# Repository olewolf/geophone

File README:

Geophone is an amplifier and a frequency analyzer for geometric sensors
such as the SM-24 geophone element from ION Geophysical Corp.

The amplifier is provided as an Arduino shield and the frequency analyzer is
implemented in software on the Arduino.  Because of the memory usage an
Arduino Mega or an Arduino Due is required.  Other Arduino versions with
at least 4 Kbytes of SRAM will require modifications in the code.

The Arduino code is richly commented and should be easy to understand and/or
modify.

For the Arduino Mega, use a single-supply operational amplifier capable of
working at 5V (such as an OP213) and set a jumper on JP3 to 5V mode.  For
the Arduino Due, use a single-supply operational amplifier working at 3.3V
(such as a TLC272 or an LT1215) to avoid damaging the Arduino's analog input.
JP3 should be placed in 3.3 mode.

Every second the Arduino software reports frequency components from 0 to 256
Hz and their measured amplitudes for amplitudes that exceed a programmed
threshold over the serial port.  The amplitudes are not calibrated; you will
have to perform a calibration yourself to translate the amplitudes into
ground movement in, e.g., meters per second.

The threshold may be changed by transmitting a new value followed by a
newline character.  The threshold is stored in EEPROM.

The frequency analysis lends itself directly to a 3D (or colored) time/
frequency plot that displays the intensities of different frequencies versus
time.  The Scilab script geoplot.sce reads a log file with the output and
generates such an image; geophone.log is a short sample of the output.

Geosampler.ino is a simple piece of software that samples the geophone
output at a rate of 512 samples per second and outputs the values over the
serial port.

read-serial-log.c provides sample C code that reads the serial output from
Geophone.ino and adds a timestamp.  The output may be plotted using the
createheatmap.pl perl script, which generates a JPEG file with the graphical
output.

Inquiries via the Github issue tracker, please.  This way, others may benefit
from the answers.

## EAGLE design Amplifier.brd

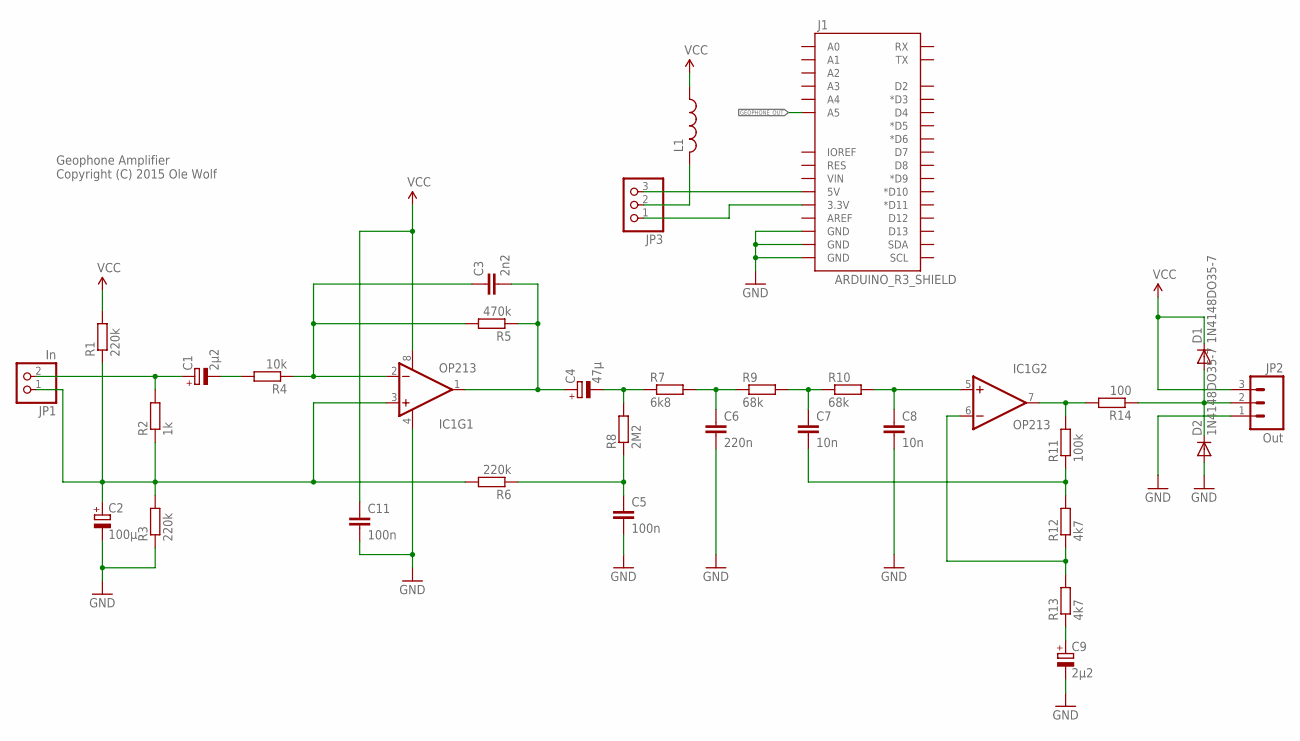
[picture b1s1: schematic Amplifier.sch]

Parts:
C1, C9: 2µ2; E2-5
C2: 100µ; E2-5
C3: 2n2; C025-025X050
C4: 47µ; E2-5
C5, C11: 100n; C025-025X050
C6: 220n; C025-025X050
C7, C8: 10n; C025-025X050
D1, D2: 1N4148DO35-7; DO35-7
IC1: OP213; DIP08
J1: ARDUINO_R3_SHIELD; UNO_R3_SHIELD
JP1: In; 1X02
JP2: Out; 1X03_LONGPADS
JP3: PINHD-1X3; 1X03
L1: L-US0207/2V; 0207/2V
R1, R3, R6: 220k; 0207/12
R2: 1k; 0207/12
R4: 10k; 0207/12
R5: 470k; 0207/12
R7: 6k8; 0207/12
R8: 2M2; 0207/12
R9, R10: 68k; 0207/12
R11: 100k; 0207/12
R12, R13: 4k7; 0207/12
R14: 100; 0207/12

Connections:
GEOPHONE_OUT: D1.A, D2.C, J1.A5, JP2.2, R14.1
GND: C2.-, C5.2, C6.2, C8.2, C9.-, C11.2, D2.A, IC1.4 (V-), J1.GND@0 (GND), J1.GND@1 (GND), J1.GND@2 (GND), JP2.1, R3.1
unnamed: C2.+, IC1.3 (+IN), JP1.1, R1.1, R2.1, R3.2, R6.2
unnamed: C1.-, R4.2
unnamed: C5.1, R6.1, R8.1
unnamed: C3.1, IC1.2 (-IN), R4.1, R5.2
unnamed: C1.+, JP1.2, R2.2
unnamed: C6.1, R7.2, R9.1
unnamed: JP3.2, L1.2
unnamed: IC1.6 (-IN), R12.1, R13.2
unnamed: C3.2, C4.+, IC1.1 (OUT), R5.1
unnamed: C4.-, R7.1, R8.2
unnamed: C7.1, R9.2, R10.1
unnamed: C9.+, R13.1
unnamed: C8.1, IC1.5 (+IN), R10.2
unnamed: J1.3.3V, JP3.1
unnamed: C7.2, R11.1, R12.2
unnamed: IC1.7 (OUT), R11.2, R14.2
unnamed: J1.5V, JP3.3
VCC: C11.1, D1.C, IC1.8 (V+), JP2.3, L1.1, R1.2

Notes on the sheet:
Geophone Amplifier Copyright (C) 2015 Ole Wolf

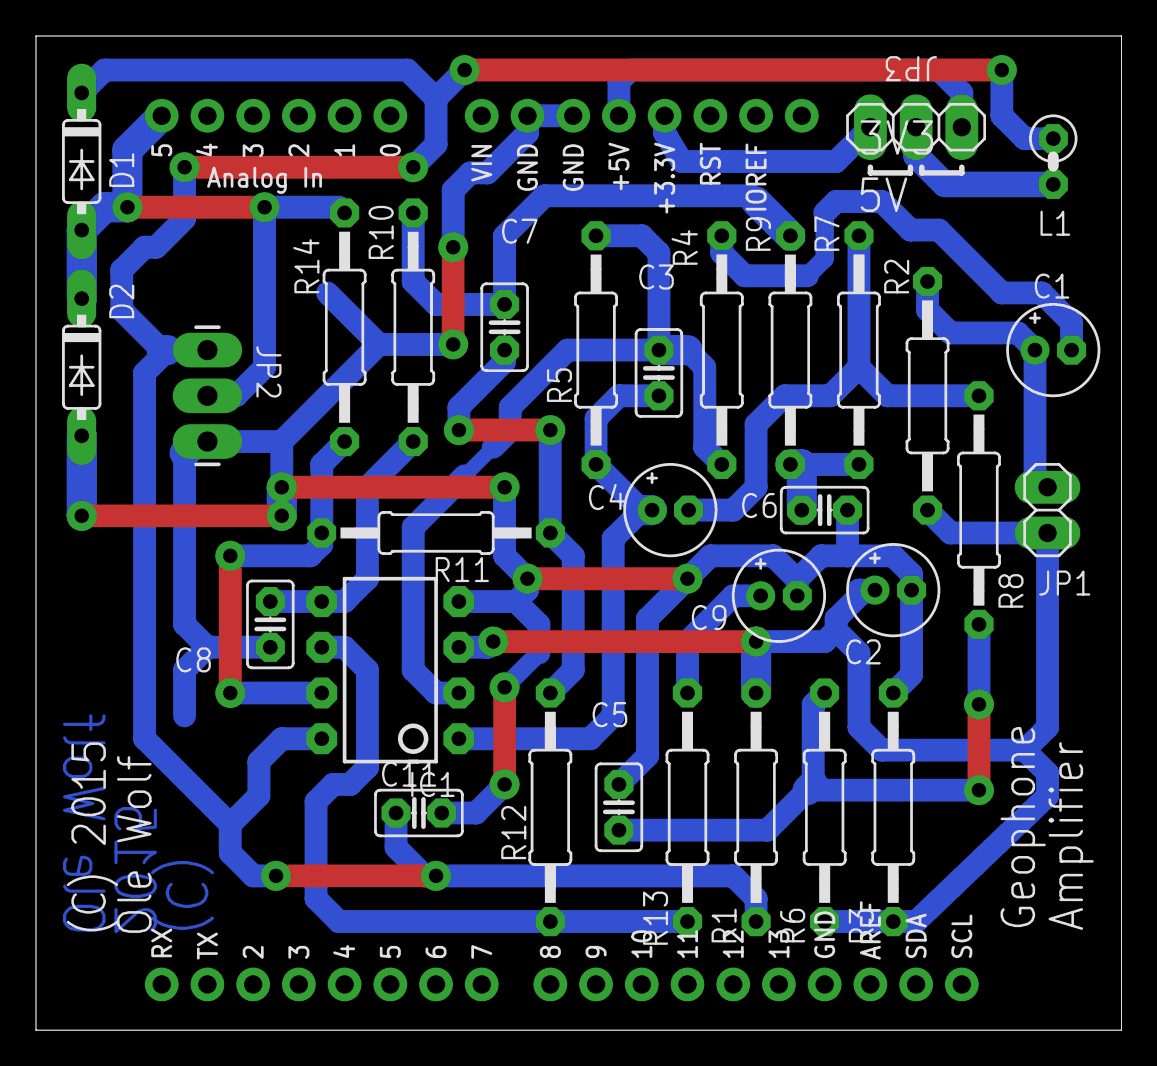
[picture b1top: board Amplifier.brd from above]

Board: 2 copper layers, 60.3 x 55.2 mm, 32 parts (0 on the bottom side), 20 nets.

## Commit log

2015-02-12 Initial commit.
2015-02-12 Bug fixed
2015-02-12 Sample output from Scilab added
2015-02-12 Non-existing files removed from ignore list
2015-02-13 Perl script to generate a heatmap image added
2015-02-13 Axes partly added
2015-02-14 Simple audio sampler added
2015-02-14 Fast clearing of the imaginary buffer, interrupts for the Mega hopefully fixed.
2015-02-14 Prepared for log files beginning with time stamps (untested).
2015-02-14 Heatmap generator handles timestamped log (sample log file added, too).
2015-02-17 Arduino Mega functionality confirmed. Prepared for XBee serial (disabled via #define in code).
2015-02-17 A few comments fixed
2015-02-17 PDF files for the schematic and PCB added
2015-02-17 Leftover from a test fixed.
2015-02-17 Incoming XBee frame parsing seems to function.
2015-02-18 Scaling factor changed
2015-02-18 Hamming window disabled because it attenuates the data too much
2015-02-24 Hamming window removed. More XBee work, still not tested.
2015-02-25 XBee frame header bug fixed. First XBee frames successfully transmitted and received.
2015-02-25 Stupid bug in output stage fixed
2015-02-26 Bug in output stage fixed, redundant capacitor removed.
2015-02-26 DC offset compensation added. Q.15 multiplication bug fixed.
2015-02-26 Index error bug preventing the last component from being plotted fixed
2015-02-26 Hamming window reapplied.
2015-02-26 Checksum added to human-readable output.
2015-02-26 Sample code for reading the serial output added.
2015-02-26 Two hours of real samples processed with read-serial-log and createheatmap.pl.
2015-03-06 Log filter script that selects a range of datestamps added.
2015-03-06 Output image specified on command line
2015-03-07 Regex fixed for dates before 10th of month.
2015-03-07 Output made unbuffered
2015-03-07 Blurring decreased slightly
2015-03-26 Starts over if the serial port is closed.
2015-03-26 Don't exit if an error occurs.
2015-03-27 Removed the endless loop and exit on failure anyway.
2015-03-29 Date::Parse dependency removed
2015-03-29 Date::Parse removed from filter-log.pl
2015-03-30 Progress counter added.
2015-03-30 from_date bug fixed.
2015-03-30 Bitbake recipe for an OpenEmbedded system added
2015-03-31 Minor bug fixes
2015-03-31 Appears to work on a proprietary AT91SAM9G25 based board
2015-04-03 Heatmap saved as PNG rather than JPEG.
2015-04-03 Minor bug fixes, LED indicator added. Imagemagick recipe removed.
2015-04-05 Watchdog added for a board where connman crashes every now and then.
2016-03-16 Closes issue #1 regarding prog_const_int16 not recognized by the compiler
2016-03-24 Issues communication note added

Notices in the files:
parts and their libraries:
SparkFun-Connectors: Licensing: Creative Commons ShareAlike 4.0 International - https://creativecommons.org/licenses/by-sa/4.0
